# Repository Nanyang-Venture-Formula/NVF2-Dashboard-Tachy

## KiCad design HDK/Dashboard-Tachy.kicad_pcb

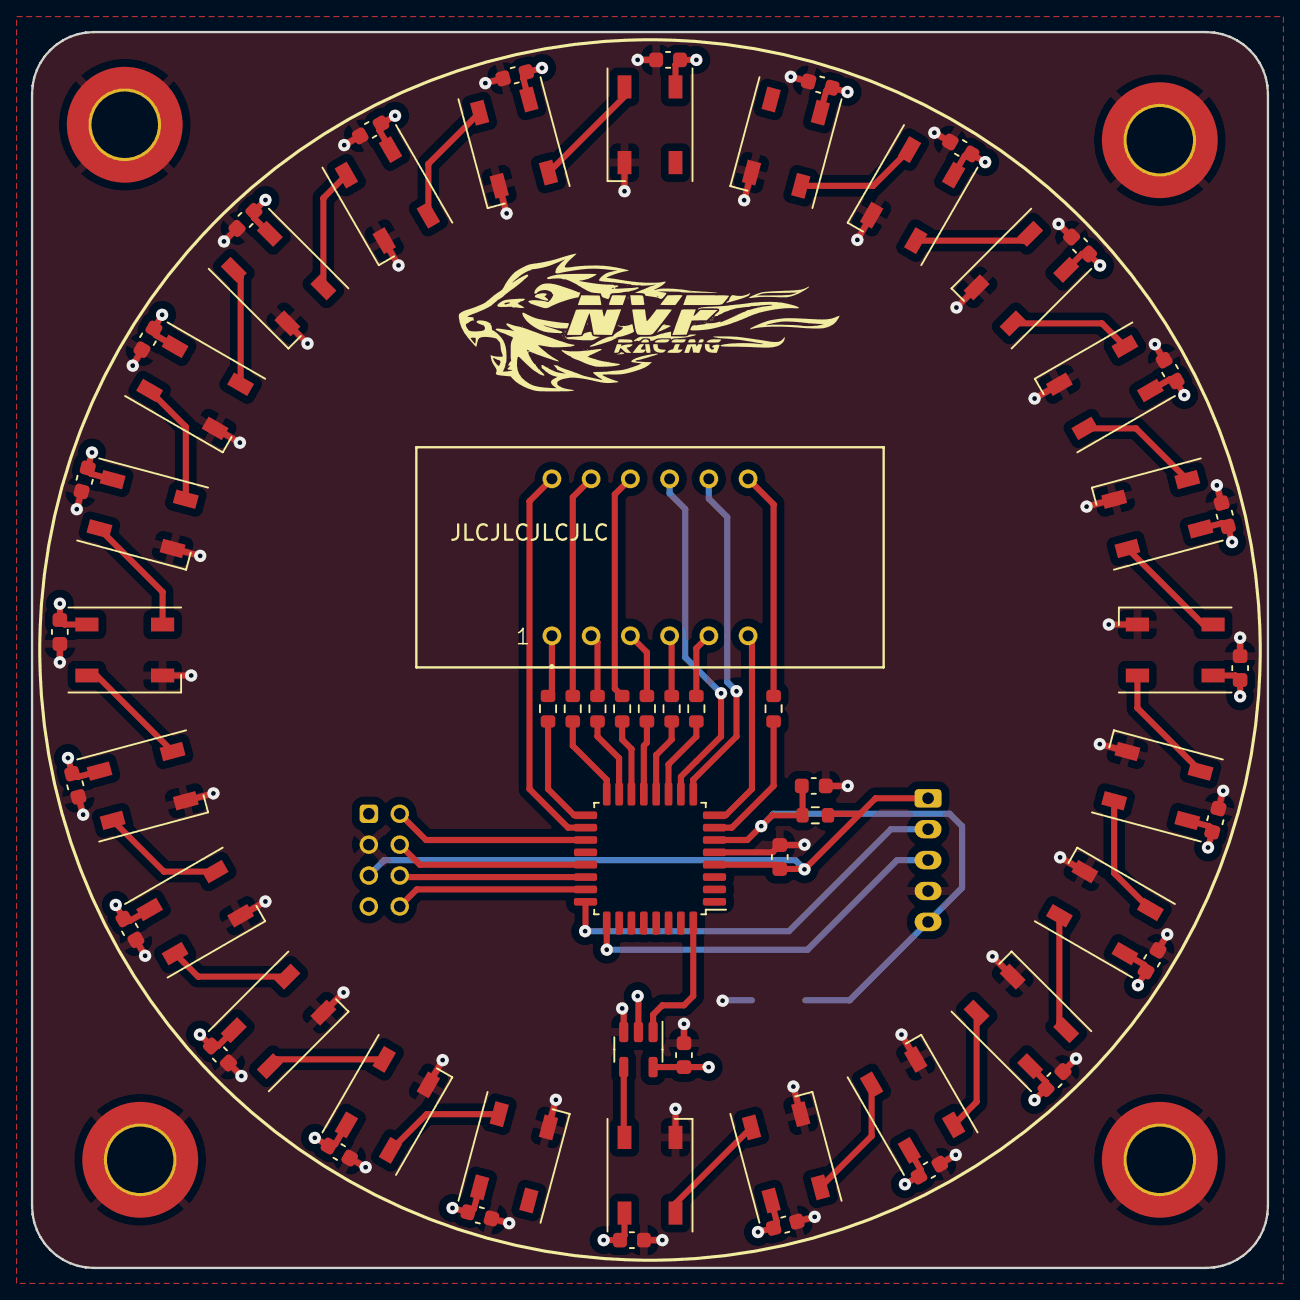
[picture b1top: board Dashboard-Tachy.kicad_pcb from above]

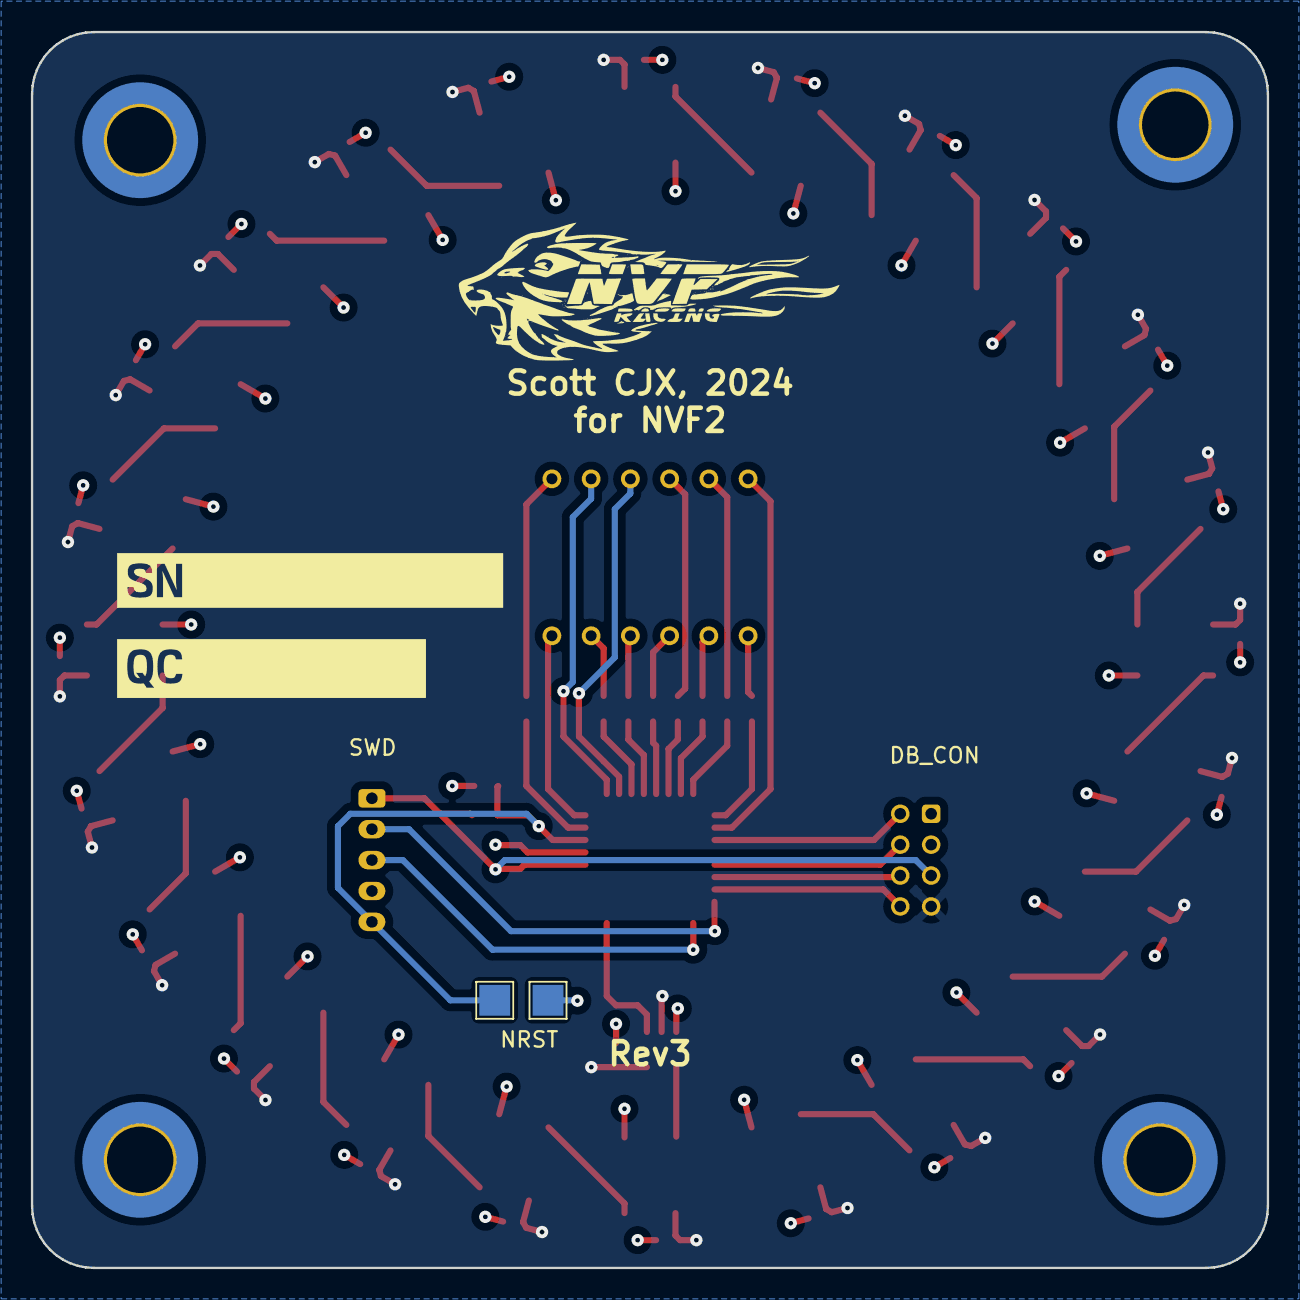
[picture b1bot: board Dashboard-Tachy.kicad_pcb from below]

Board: 2 copper layers, 80.0 x 80.0 mm, 73 parts (6 on the bottom side), 55 nets.

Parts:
C101, C102, C103, C104, C105, C106, C107, C108, C109, C110, C111, C112, C113, C114, C115, C116, C117, C118, C119, C120, C121, C122, C123, C124, C125, C126, C127: 100n; C_0603_1608Metric
D101, D102, D103, D104, D105, D106, D107, D108, D109, D110, D111, D112, D113, D114, D115, D116, D117, D118, D119, D120, D121, D122, D123, D124: WS2812B; LED_WS2812B_PLCC4_5.0x5.0mm_P3.2mm
H101, H102, H103, H104: MountingHole_Pad; MountingHole_4.3mm_M4_DIN965_Pad_TopBottom
J101: Conn_02x04_Odd_Even; PHD_02x04V-H
R101, R102, R103, R104, R105, R106, R107, R108: 220; R_0603_1608Metric
R109: 10k; R_0603_1608Metric
SWD101: SWD_Breakout_Minimal; PH_01x05V-H
TP101, TP102: TestPoint; TestPoint_Pad_2.0x2.0mm
U101: LDQ-M3604RI; 04x7SegmentDispl
U102: STM32G030K6Tx; LQFP-32_7x7mm_P0.8mm
U103: 74LVC1G00; SOT-23-5
kibuzzard-65BA7346: G***; kibuzzard-65BA7346
kibuzzard-65BA7359: G***; kibuzzard-65BA7359

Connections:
+3V3: C125.2, J101.5, R109.2, SWD101.1 (3V3), U102.4 (VDD)
+5V: C101.1, C102.1, C103.1, C104.1, C105.1, C106.1, C107.1, C108.1, C109.1, C110.1, C111.1, C112.1, C113.1, C114.1, C115.1, C116.1, C117.1, C118.1, C119.1, C120.1, C121.1, C122.1, C123.1, C124.1, C126.2, D101.1 (VDD), D102.1 (VDD), D103.1 (VDD), D104.1 (VDD), D105.1 (VDD), D106.1 (VDD), D107.1 (VDD), D108.1 (VDD), D109.1 (VDD), D110.1 (VDD), D111.1 (VDD), D112.1 (VDD), D113.1 (VDD), D114.1 (VDD), D115.1 (VDD), D116.1 (VDD), D117.1 (VDD), D118.1 (VDD), D119.1 (VDD), D120.1 (VDD), D121.1 (VDD), D122.1 (VDD), D123.1 (VDD), D124.1 (VDD), J101.7, U103.2, U103.5 (VCC)
/7SEG_A: R101.1, U101.11 (a)
/7SEG_B: R102.1, U101.7 (b)
/7SEG_C: R103.1, U101.4 (c)
/7SEG_CA1: U101.12 (CA1), U102.18 (PA8)
/7SEG_CA2: U101.9 (CA2), U102.10 (PA3)
/7SEG_CA3: U101.8 (CA3), U102.9 (PA2)
/7SEG_CA4: U101.6 (CA4), U102.8 (PA1)
/7SEG_D: R104.1, U101.2 (d)
/7SEG_DP: R108.1, U101.3 (DPX)
/7SEG_E: R105.1, U101.1 (e)
/7SEG_F: R106.1, U101.10 (f)
/7SEG_G: R107.1, U101.5 (g)
/I2C_SCL: J101.6, U102.22 (PA11/PA9)
/I2C_SDA: J101.8, U102.23 (PA12/PA10)
/LED-0-1: D101.4 (DIN), U103.4
/LED-1-2: D101.2 (DOUT), D102.4 (DIN)
/LED-2-3: D102.2 (DOUT), D103.4 (DIN)
/LED-3-4: D103.2 (DOUT), D104.4 (DIN)
/LED-4-5: D104.2 (DOUT), D105.4 (DIN)
/LED-5-6: D105.2 (DOUT), D106.4 (DIN)
/LED-6-7: D106.2 (DOUT), D107.4 (DIN)
/LED-7-8: D107.2 (DOUT), D108.4 (DIN)
/LED-8-9: D108.2 (DOUT), D109.4 (DIN)
/LED-9-10: D109.2 (DOUT), D110.4 (DIN)
/LED-10-11: D110.2 (DOUT), D111.4 (DIN)
/LED-11-12: D111.2 (DOUT), D112.4 (DIN)
/LED-12-13: D112.2 (DOUT), D113.4 (DIN)
/LED-13-14: D113.2 (DOUT), D114.4 (DIN)
/LED-14-15: D114.2 (DOUT), D115.4 (DIN)
/LED-15-16: D115.2 (DOUT), D116.4 (DIN)
/LED-16-17: D116.2 (DOUT), D117.4 (DIN)
/LED-17-18: D117.2 (DOUT), D118.4 (DIN)
/LED-18-19: D118.2 (DOUT), D119.4 (DIN)
/LED-19-20: D119.2 (DOUT), D120.4 (DIN)
/LED-20-21: D120.2 (DOUT), D121.4 (DIN)
/LED-21-22: D121.2 (DOUT), D122.4 (DIN)
/LED-22-23: D122.2 (DOUT), D123.4 (DIN)
/LED-23-24: D123.2 (DOUT), D124.4 (DIN)
/NEOPIX: U102.32 (PB8), U103.1
/NRST: C127.2, R109.1, SWD101.5 (RST), TP101.1, U102.6 (NRST)
/SWCLK: SWD101.3 (SWCLK), U102.25 (PA14)
/SWDIO: SWD101.2 (SWDIO), U102.24 (PA13)
/UART_RX: J101.4, U102.21 (PA10/NC)
/UART_TX: J101.2, U102.19 (PA9/NC)
GND: C101.2, C102.2, C103.2, C104.2, C105.2, C106.2, C107.2, C108.2, C109.2, C110.2, C111.2, C112.2, C113.2, C114.2, C115.2, C116.2, C117.2, C118.2, C119.2, C120.2, C121.2, C122.2, C123.2, C124.2, C125.1, C126.1, C127.1, D101.3 (VSS), D102.3 (VSS), D103.3 (VSS), D104.3 (VSS), D105.3 (VSS), D106.3 (VSS), D107.3 (VSS), D108.3 (VSS), D109.3 (VSS), D110.3 (VSS), D111.3 (VSS), D112.3 (VSS), D113.3 (VSS), D114.3 (VSS), D115.3 (VSS), D116.3 (VSS), D117.3 (VSS), D118.3 (VSS), D119.3 (VSS), D120.3 (VSS), D121.3 (VSS), D122.3 (VSS), D123.3 (VSS), D124.3 (VSS), H101.1, H102.1, H103.1, H104.1, J101.3, SWD101.4 (GND), TP102.1, U102.5 (VSS), U103.3 (GND)
unnamed: R102.2, U102.7 (PA0)
unnamed: R107.2, U102.11 (PA4)
unnamed: R103.2, U102.12 (PA5)
unnamed: R108.2, U102.13 (PA6)
unnamed: R106.2, U102.14 (PA7)
unnamed: R104.2, U102.15 (PB0)
unnamed: R101.2, U102.16 (PB1)
unnamed: R105.2, U102.17 (PB2)

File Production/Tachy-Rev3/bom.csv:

Designator,Footprint,Quantity,Value,LCSC Part #
"C101, C102, C103, C104, C105, C106, C107, C108, C109, C110, C111, C112, C113, C114, C115, C116, C117, C118, C119, C120, C121, C122, C123, C124, C125, C126, C127",0603,27,100n,C14663
"D101, D102, D103, D104, D105, D106, D107, D108, D109, D110, D111, D112, D113, D114, D115, D116, D117, D118, D119, D120, D121, D122, D123, D124",LED_WS2812B_PLCC4_5.0x5.0mm_P3.2mm,24,WS2812B,C2843785
J101,PHD_02x04V-H,1,Conn_02x04_Odd_Even,-
"R101, R102, R103, R104, R105, R106, R107, R108",0603,8,220,C22962
R109,0603,1,10k,C25804
SWD101,PH_01x05V-H,1,SWD_Breakout_Minimal,-
"TP101, TP102",TestPoint_Pad_2.0x2.0mm,2,TestPoint,-
U101,04x7SegmentDispl,1,LDQ-M3604RI,-
U102,LQFP-32_7x7mm_P0.8mm,1,STM32G030K6Tx,C529331
U103,SOT-23-5,1,74LVC1G00,C434066

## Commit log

2024-01-23 Initialize gh-pages
2024-01-23 Moving files docs/* LICENSE using main
2024-01-23 Deploying to gh-pages from @ Nanyang-Venture-Formula/NVF2-Dashboard-Tachy@56d404b16f9ceed5c92db0b7c61674dc5c889b3f 🚀
2024-01-23 Deploying to gh-pages from @ Nanyang-Venture-Formula/NVF2-Dashboard-Tachy@9a2c9f258144002a258f65ed5e4d252bd401a341 🚀
2024-01-23 refactored
2024-01-23 Deploying to gh-pages from @ Nanyang-Venture-Formula/NVF2-Dashboard-Tachy@2f9e2d19fbdf1efe438d395afa950490e9a97ff4 🚀
2024-01-23 Deploying to gh-pages from @ Nanyang-Venture-Formula/NVF2-Dashboard-Tachy@d3d39bb59c9c2929dbdcd71535f9638054252239 🚀
2024-01-24 updated ignore
2024-01-24 Deploying to gh-pages from @ Nanyang-Venture-Formula/NVF2-Dashboard-Tachy@b391c8811bb6ee70311633fdb3d8ad6290521fdc 🚀
2024-01-24 updated gitignore
2024-01-24 Deploying to gh-pages from @ Nanyang-Venture-Formula/NVF2-Dashboard-Tachy@d684206f70b98384ee46a09fd32e040918d32c5e 🚀
2024-01-25 set rev1
2024-01-25 Deploying to gh-pages from @ Nanyang-Venture-Formula/NVF2-Dashboard-Tachy@9efc1e5c07bf48e9f17abce693450108ebc3cca9 🚀
2024-01-25 updated rev1.1
2024-01-25 Deploying to gh-pages from @ Nanyang-Venture-Formula/NVF2-Dashboard-Tachy@b6f15581ff201165284f3bca7c060f40dd1f294a 🚀
2024-01-25 Deploying to gh-pages from @ Nanyang-Venture-Formula/NVF2-Dashboard-Tachy@2a34ed7a7699af27c0e706cdd4b9ccf31978c664 🚀
2024-01-25 updated REV1.1 docs
2024-01-25 Deploying to gh-pages from @ Nanyang-Venture-Formula/NVF2-Dashboard-Tachy@acc7c23aaa4bb68937e490403b71177a212c47f4 🚀
2024-01-31 added fab
2024-01-31 Deploying to gh-pages from @ Nanyang-Venture-Formula/NVF2-Dashboard-Tachy@3ce2bf10bd235f01bbfb8f34ef3bd4dd27b5555e 🚀
2024-02-05 updated dimensions
2024-02-05 changed outline
